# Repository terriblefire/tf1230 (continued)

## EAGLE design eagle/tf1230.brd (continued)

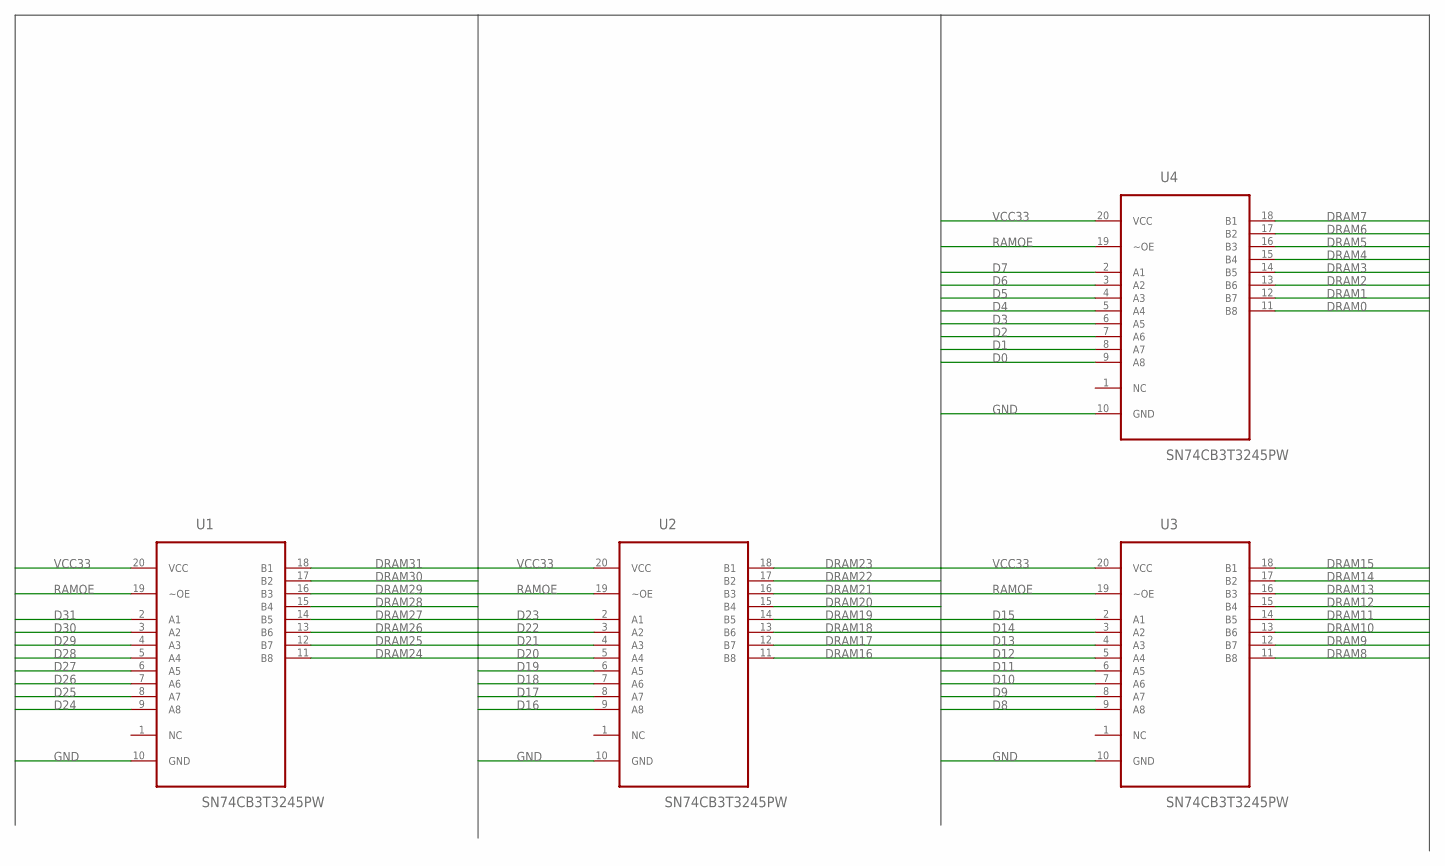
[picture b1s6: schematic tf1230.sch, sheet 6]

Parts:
U1, U2, U3, U4: SN74CB3T3245PW; SOP65P640X120-20N

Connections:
D0: U4.9 (A8); also elsewhere on the board
D1: U4.8 (A7); also elsewhere on the board
D2: U4.7 (A6); also elsewhere on the board
D3: U4.6 (A5); also elsewhere on the board
D4: U4.5 (A4); also elsewhere on the board
D5: U4.4 (A3); also elsewhere on the board
D6: U4.3 (A2); also elsewhere on the board
D7: U4.2 (A1); also elsewhere on the board
D8: U3.9 (A8); also elsewhere on the board
D9: U3.8 (A7); also elsewhere on the board
D10: U3.7 (A6); also elsewhere on the board
D11: U3.6 (A5); also elsewhere on the board
D12: U3.5 (A4); also elsewhere on the board
D13: U3.4 (A3); also elsewhere on the board
D14: U3.3 (A2); also elsewhere on the board
D15: U3.2 (A1); also elsewhere on the board
D16: U2.9 (A8); also elsewhere on the board
D17: U2.8 (A7); also elsewhere on the board
D18: U2.7 (A6); also elsewhere on the board
D19: U2.6 (A5); also elsewhere on the board
D20: U2.5 (A4); also elsewhere on the board
D21: U2.4 (A3); also elsewhere on the board
D22: U2.3 (A2); also elsewhere on the board
D23: U2.2 (A1); also elsewhere on the board
D24: U1.9 (A8); also elsewhere on the board
D25: U1.8 (A7); also elsewhere on the board
D26: U1.7 (A6); also elsewhere on the board
D27: U1.6 (A5); also elsewhere on the board
D28: U1.5 (A4); also elsewhere on the board
D29: U1.4 (A3); also elsewhere on the board
D30: U1.3 (A2); also elsewhere on the board
D31: U1.2 (A1); also elsewhere on the board
DRAM0: U4.11 (B8); also elsewhere on the board
DRAM1: U4.12 (B7); also elsewhere on the board
DRAM2: U4.13 (B6); also elsewhere on the board
DRAM3: U4.14 (B5); also elsewhere on the board
DRAM4: U4.15 (B4); also elsewhere on the board
DRAM5: U4.16 (B3); also elsewhere on the board
DRAM6: U4.17 (B2); also elsewhere on the board
DRAM7: U4.18 (B1); also elsewhere on the board
DRAM8: U3.11 (B8); also elsewhere on the board
DRAM9: U3.12 (B7); also elsewhere on the board
DRAM10: U3.13 (B6); also elsewhere on the board
DRAM11: U3.14 (B5); also elsewhere on the board
DRAM12: U3.15 (B4); also elsewhere on the board
DRAM13: U3.16 (B3); also elsewhere on the board
DRAM14: U3.17 (B2); also elsewhere on the board
DRAM15: U3.18 (B1); also elsewhere on the board
DRAM16: U2.11 (B8); also elsewhere on the board
DRAM17: U2.12 (B7); also elsewhere on the board
DRAM18: U2.13 (B6); also elsewhere on the board
DRAM19: U2.14 (B5); also elsewhere on the board
DRAM20: U2.15 (B4); also elsewhere on the board
DRAM21: U2.16 (B3); also elsewhere on the board
DRAM22: U2.17 (B2); also elsewhere on the board
DRAM23: U2.18 (B1); also elsewhere on the board
DRAM24: U1.11 (B8); also elsewhere on the board
DRAM25: U1.12 (B7); also elsewhere on the board
DRAM26: U1.13 (B6); also elsewhere on the board
DRAM27: U1.14 (B5); also elsewhere on the board
DRAM28: U1.15 (B4); also elsewhere on the board
DRAM29: U1.16 (B3); also elsewhere on the board
DRAM30: U1.17 (B2); also elsewhere on the board
DRAM31: U1.18 (B1); also elsewhere on the board
GND: U1.10 (GND), U2.10 (GND), U3.10 (GND), U4.10 (GND); also elsewhere on the board
RAMOE: U1.19 (~OE), U2.19 (~OE), U3.19 (~OE), U4.19 (~OE); also elsewhere on the board
VCC33: U1.20 (VCC), U2.20 (VCC), U3.20 (VCC), U4.20 (VCC); also elsewhere on the board

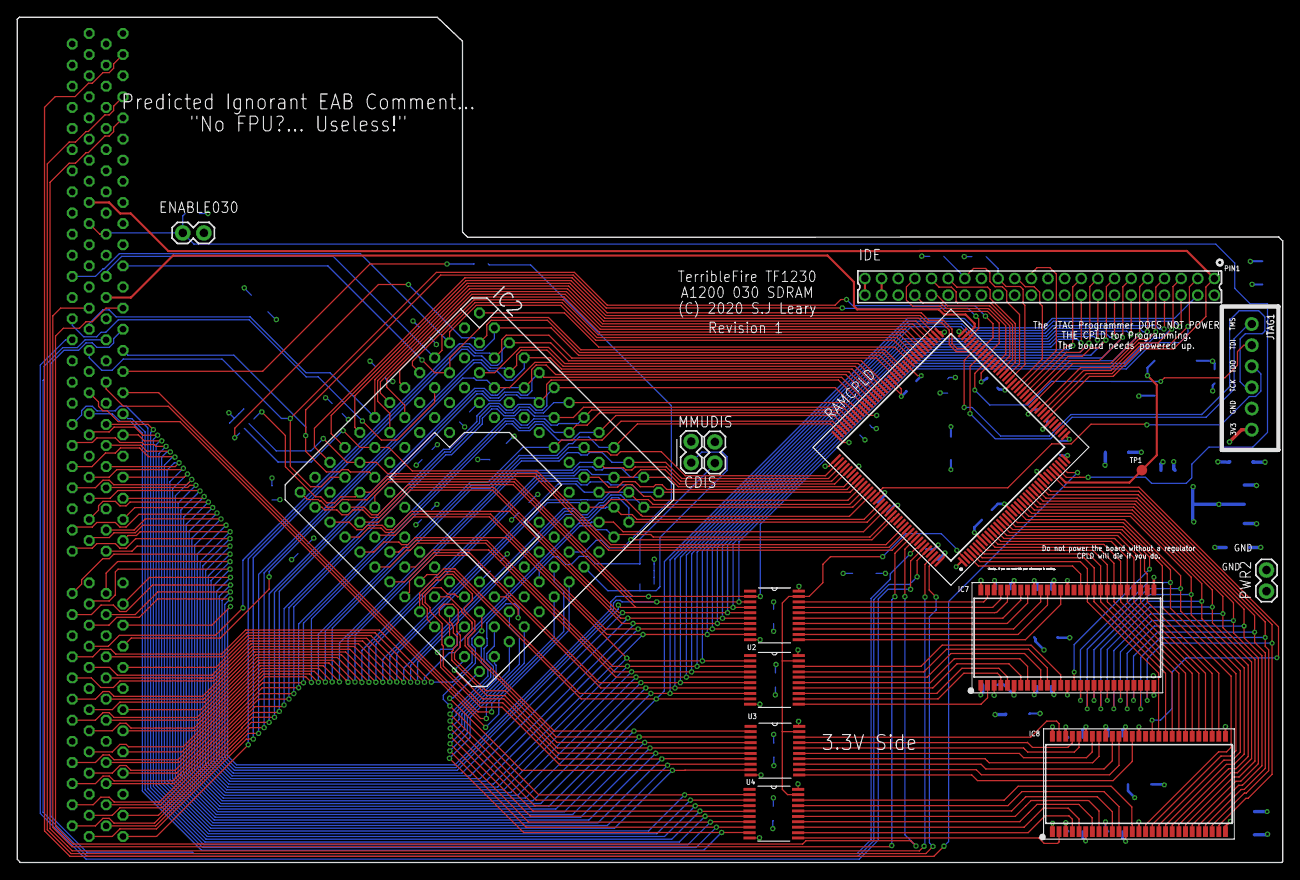
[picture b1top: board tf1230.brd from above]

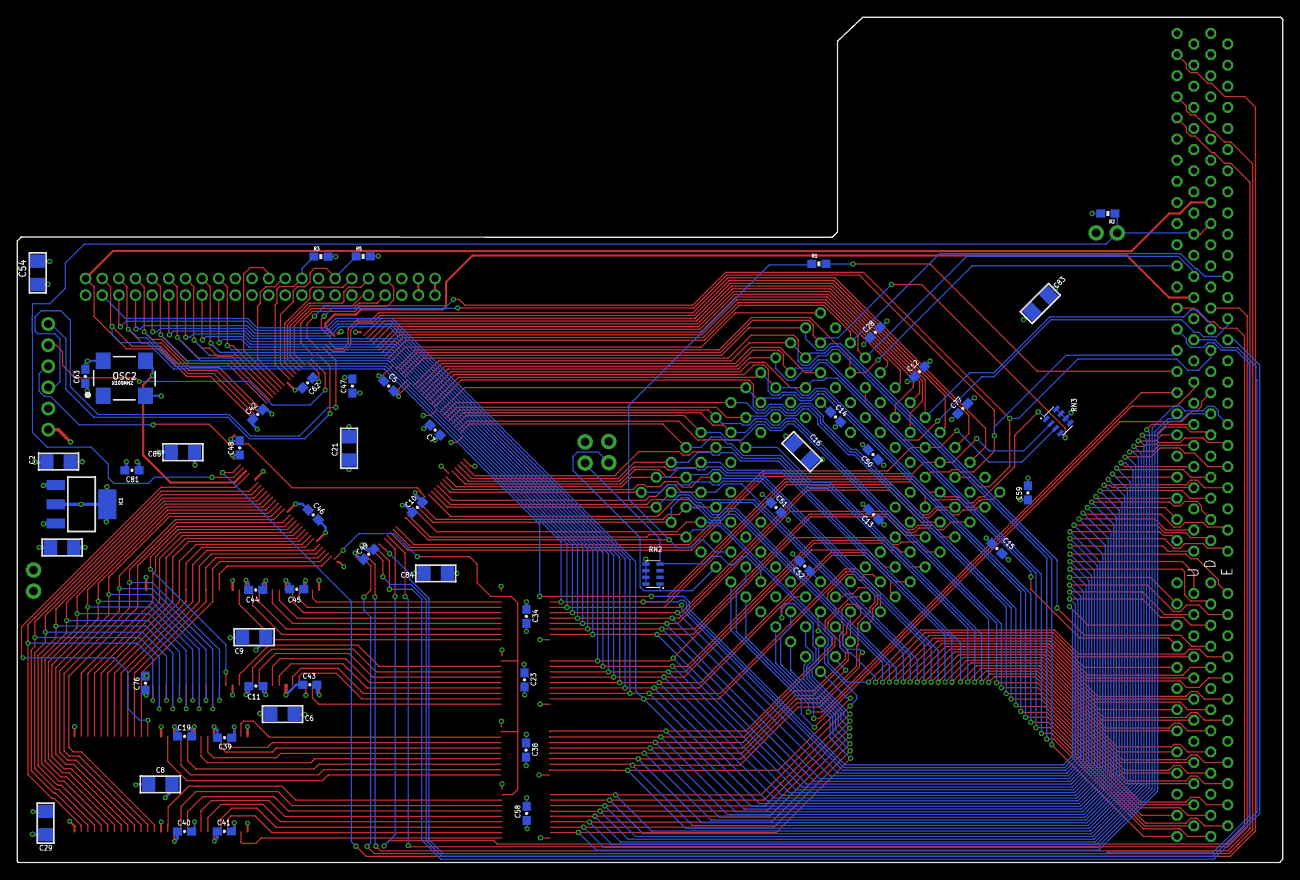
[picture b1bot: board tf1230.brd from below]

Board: 4 copper layers, 152.1 x 101.6 mm, 70 parts (55 on the bottom side), 178 nets.

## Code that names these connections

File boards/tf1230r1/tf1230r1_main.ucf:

# Copyright (C) 2016-2017, Stephen J. Leary
# All rights reserved.
#
# This file is part of TF330/TF120 (Terrible Fire 030 Accelerator)
#
# TF330/TF120 is free software: you can redistribute it and/or modify
# it under the terms of the GNU General Public License as published by
# the Free Software Foundation, either version 3 of the License, or
# (at your option) any later version.
#
# TF330/TF120 is distributed in the hope that it will be useful,
# but WITHOUT ANY WARRANTY; without even the implied warranty of
# MERCHANTABILITY or FITNESS FOR A PARTICULAR PURPOSE.  See the
# GNU General Public License for more details.
#
# You should have received a copy of the GNU General Public License
# along with TF1230. If not, see <http://www.gnu.org/licenses/>.

#Clocks
NET "CLK100M"		LOC="32";
NET "CLK100M" BUFG=CLK;
NET "CLK100M" TNM_NET = "CLK100M"; # gives the net clk a group name as CLK100M

NET "A<0>"      LOC="87";
NET "A<1>"      LOC="95";
NET "A<2>"      LOC="128";
NET "A<3>"      LOC="126";
NET "A<4>"      LOC="125";
NET "A<5>"      LOC="124";
NET "A<6>"      LOC="121";
NET "A<7>"      LOC="120";
NET "A<8>"      LOC="119";
NET "A<9>"      LOC="118";
NET "A<10>"      LOC="117";
NET "A<11>"      LOC="116";
NET "A<12>"      LOC="113";
NET "A<13>"      LOC="115";
NET "A<14>"      LOC="112";
NET "A<15>"      LOC="111";
NET "A<16>"      LOC="110";
NET "A<17>"      LOC="107";
NET "A<18>"      LOC="106";
NET "A<19>"      LOC="105";
NET "A<20>"      LOC="104";
NET "A<21>"      LOC="103";
NET "A<22>"      LOC="102";
NET "A<23>"      LOC="101";
NET "A<24>"      LOC="100";
NET "A<25>"      LOC="98";
NET "A<26>"      LOC="97";
NET "A<27>"      LOC="96";
NET "A<28>"      LOC="94";
NET "A<29>"      LOC="93";
NET "A<30>"      LOC="91";
NET "A<31>"      LOC="88";
NET "AB<2>"      LOC="59";
NET "AB<3>"      LOC="58";
NET "AB<4>"      LOC="60";
NET "ARAM<0>"      LOC="25";
NET "ARAM<1>"      LOC="26";
NET "ARAM<2>"      LOC="27";
NET "ARAM<3>"      LOC="28";
NET "ARAM<4>"      LOC="14";
NET "ARAM<5>"      LOC="13";
NET "ARAM<6>"      LOC="12";
NET "ARAM<7>"      LOC="11";
NET "ARAM<8>"      LOC="10";
NET "ARAM<9>"      LOC="9";
NET "ARAM<10>"      LOC="24";
NET "ARAM<11>"      LOC="7";
NET "ARAM<12>"      LOC="6";
NET "AS20"      LOC="140";
NET "AS30"      LOC="132";
NET "BA<0>"      LOC="23";
NET "BA<1>"      LOC="22";
NET "BERR"      LOC="75";
NET "BG30"      LOC="86";
NET "BGACK30"      LOC="92";
NET "BR20"      LOC="33";
NET "BR30"      LOC="83";
NET "CAS"      LOC="19";
NET "CBACK"      LOC="74";
NET "CBREQ"      LOC="68";
NET "CFGOUT"      LOC="34";
NET "CIIN"      LOC="69";
NET "CLK14M"      LOC="71";
NET "CLKCPU"      LOC="80";
NET "CLKRAM"      LOC="4";
NET "CLKRAME"      LOC="5";
NET "D<24>"      LOC="52";
NET "D<25>"      LOC="51";
NET "D<26>"      LOC="50";
NET "D<27>"      LOC="49";
NET "D<28>"      LOC="48";
NET "D<29>"      LOC="46";
NET "D<30>"      LOC="45";
NET "D<31>"      LOC="44";
NET "DQM<0>"      LOC="16";
NET "DQM<1>"      LOC="31";
NET "DQM<2>"      LOC="15";
NET "DQM<3>"      LOC="3";
NET "DS20"      LOC="139";
NET "DS30"      LOC="133";
NET "DS30ACK<0>"      LOC="79";
NET "DS30ACK<1>"      LOC="78";
NET "DSACK<0>"      LOC="135";
NET "DSACK<1>"      LOC="136";
NET "FC<0>"      LOC="85";
NET "FC<1>"      LOC="82";
NET "FC<2>"      LOC="81";
NET "HALT"      LOC="76";
NET "IDECS<0>"      LOC="64";
NET "IDECS<1>"      LOC="61";
NET "IDEINT"      LOC="57";
NET "IDEWAIT"      LOC="56";
NET "INT2"      LOC="143";
NET "IOR"      LOC="54";
NET "IOW"      LOC="53";
NET "PUNT"      LOC="142";
NET "RAMOE"     LOC="2";
NET "RAMCS"      LOC="21";
NET "RAMWE"      LOC="17";
NET "RAS"      LOC="20";
NET "RESET"      LOC="43";
NET "RSTO"      LOC="129";
NET "RW20"      LOC="138";
NET "RW30"      LOC="134";
NET "SIZ<0>"      LOC="66";
NET "SIZ<1>"      LOC="70";
NET "STERM"      LOC="77";

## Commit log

2021-10-30 Update LICENSE
2021-10-30 initial code upload
